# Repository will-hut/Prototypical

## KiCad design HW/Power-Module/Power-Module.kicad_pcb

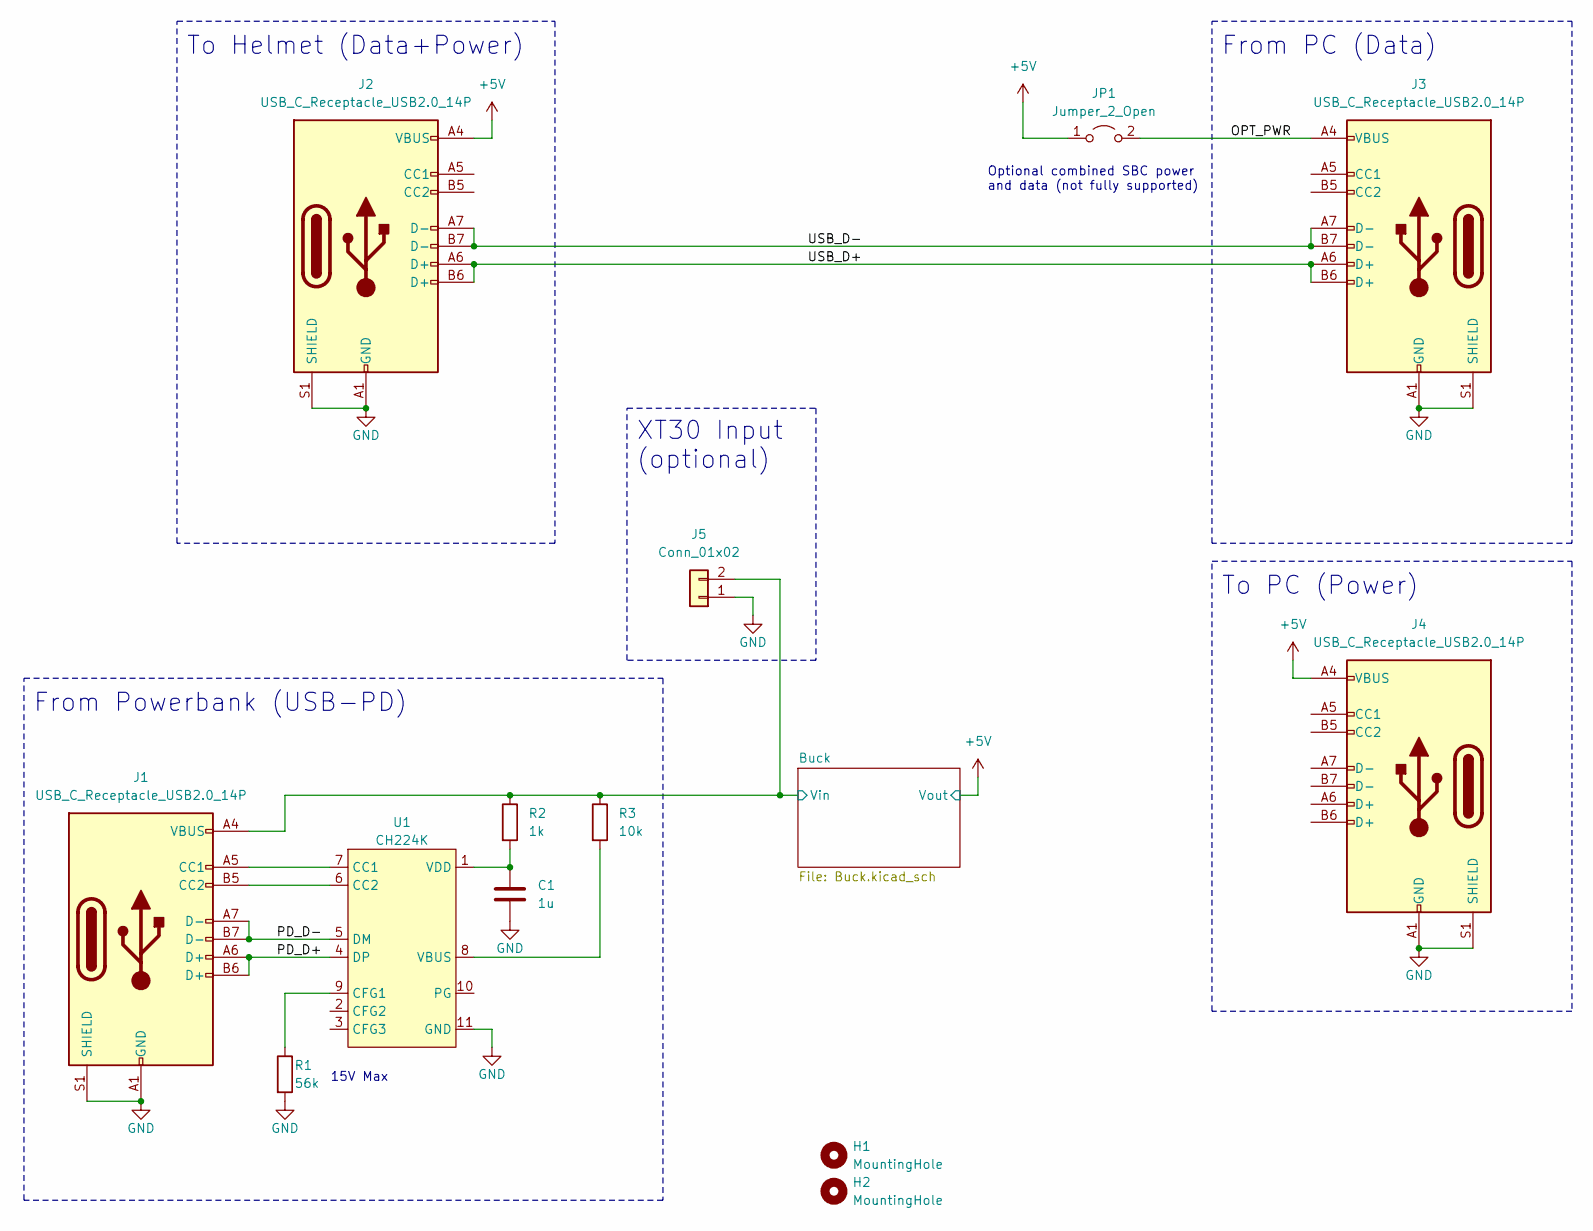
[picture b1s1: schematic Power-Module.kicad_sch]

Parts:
C1: 1u; C_0603_1608Metric; LCSC C15849
H1, H2: MountingHole; MountingHole_3.2mm_M3
J1, J2, J3, J4: USB_C_Receptacle_USB2.0_14P; USB_C_Receptacle_GCT_USB4105-xx-A_16P_TopMnt_Horizontal
J5: Conn_01x02; AMASS_XT30U-F_1x02_P5.0mm_Vertical
JP1: Jumper_2_Open; SolderJumper-2_P1.3mm_Open_Pad1.0x1.5mm
R1: 56k; R_0603_1608Metric; LCSC C23206
R2: 1k; R_0603_1608Metric; LCSC C21190
R3: 10k; R_0603_1608Metric; LCSC C25804
U1: CH224K; ESSOP-10_L4.9-W3.9-P1.0-LS6.0-TL-EP; LCSC Part C970725

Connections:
+5V: J2.A4 (VBUS), J2.A9 (VBUS), J2.B4 (VBUS), J2.B9 (VBUS), J4.A4 (VBUS), J4.A9 (VBUS), J4.B4 (VBUS), J4.B9 (VBUS), JP1.1 (A); also elsewhere on the board
/Buck/Vin: J1.A4 (VBUS), J1.A9 (VBUS), J1.B4 (VBUS), J1.B9 (VBUS), J5.2, R2.1, R3.1; also elsewhere on the board
/OPT_PWR: J3.A4 (VBUS), J3.A9 (VBUS), J3.B4 (VBUS), J3.B9 (VBUS), JP1.2 (B)
/PD_D+: J1.A6 (D+), J1.B6 (D+), U1.4 (DP)
/PD_D-: J1.A7 (D-), J1.B7 (D-), U1.5 (DM)
/USB_D+: J2.A6 (D+), J2.B6 (D+), J3.A6 (D+), J3.B6 (D+)
/USB_D-: J2.A7 (D-), J2.B7 (D-), J3.A7 (D-), J3.B7 (D-)
GND: C1.2, J1.A1 (GND), J1.A12 (GND), J1.B1 (GND), J1.B12 (GND), J1.S1 (SHIELD), J2.A1 (GND), J2.A12 (GND), J2.B1 (GND), J2.B12 (GND), J2.S1 (SHIELD), J3.A1 (GND), J3.A12 (GND), J3.B1 (GND), J3.B12 (GND), J3.S1 (SHIELD), J4.A1 (GND), J4.A12 (GND), J4.B1 (GND), J4.B12 (GND), J4.S1 (SHIELD), J5.1, R1.2, U1.11 (GND); also elsewhere on the board
unnamed: J1.A5 (CC1), U1.7 (CC1)
unnamed: J1.B5 (CC2), U1.6 (CC2)
unnamed: R1.1, U1.9 (CFG1)
unnamed: R3.2, U1.8 (VBUS)
unnamed: C1.1, R2.2, U1.1 (VDD)

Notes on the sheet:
To Helmet (Data+Power)
From PC (Data)
Optional combined SBC power and data (not fully supported)
15V Max
From Powerbank (USB-PD)
To PC (Power)
XT30 Input (optional)

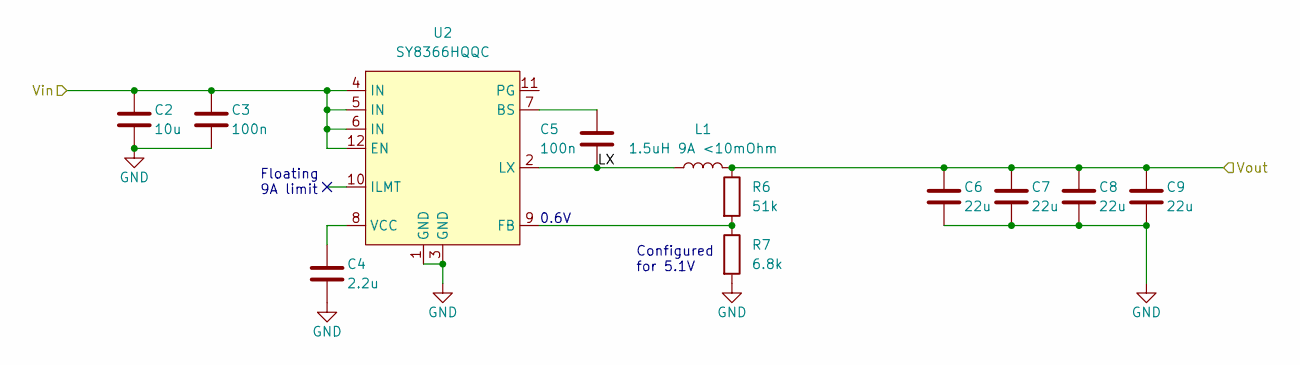
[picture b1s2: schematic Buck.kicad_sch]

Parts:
C2: 10u; C_0603_1608Metric
C3, C5: 100n; C_0603_1608Metric
C4: 2.2u; C_0603_1608Metric
C6, C7, C8, C9: 22u; C_0805_2012Metric
L1: 1.5uH 9A <10mOhm; IND-SMD_L7.0-W6.6
R6: 51k; R_0603_1608Metric
R7: 6.8k; R_0603_1608Metric
U2: SY8366HQQC; QFN-12_L3.0-W3.0-P0.45-TL-EP; LCSC Part C178253

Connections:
+5V: C6.1, C7.1, C8.1, C9.1, L1.2, R6.1; also elsewhere on the board
/Buck/LX: C5.2, L1.1, U2.2 (LX)
/Buck/Vin: C2.1, C3.1, U2.4 (IN), U2.5 (IN), U2.6 (IN), U2.12 (EN); also elsewhere on the board
GND: C2.2, C3.2, C4.2, C6.2, C7.2, C8.2, C9.2, R7.2, U2.1 (GND), U2.3 (GND); also elsewhere on the board
unnamed: C5.1, U2.7 (BS)
unnamed: R6.2, R7.1, U2.9 (FB)
unnamed: C4.1, U2.8 (VCC)

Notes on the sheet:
Floating 9A limit
0.6V
Configured for 5.1V

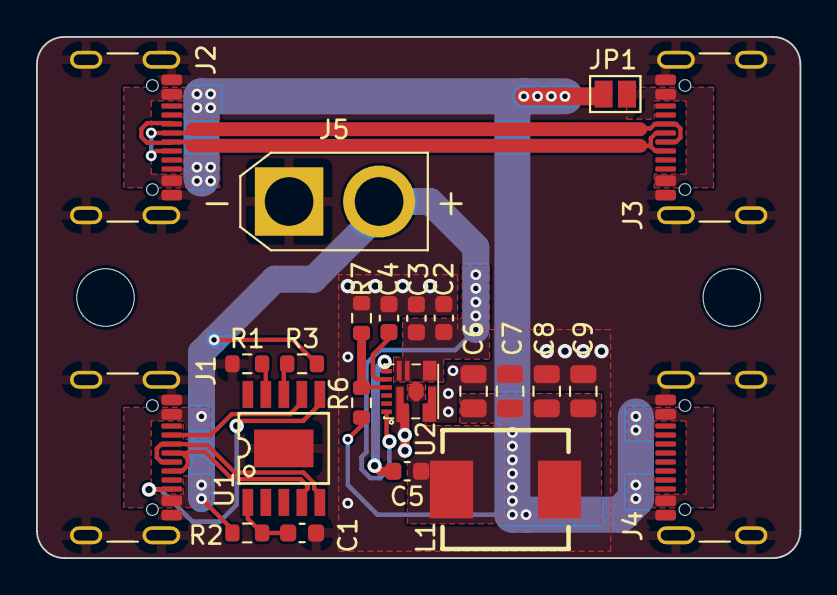
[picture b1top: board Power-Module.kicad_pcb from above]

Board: 2 copper layers, 42.4 x 29.0 mm, 25 parts (0 on the bottom side), 17 nets.

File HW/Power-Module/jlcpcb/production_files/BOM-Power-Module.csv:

Comment,Designator,Footprint,LCSC
100n,"C3,C5",C_0603_1608Metric,C14663
1u,C1,C_0603_1608Metric,C15849
1.5uH 9A <10mOhm,L1,IND-SMD_L7.0-W6.6,C167217
SY8366HQQC,U2,QFN-12_L3.0-W3.0-P0.45-TL-EP,C178253
1k,R2,R_0603_1608Metric,C21190
51k,R6,R_0603_1608Metric,C23196
56k,R1,R_0603_1608Metric,C23206
6.8k,R7,R_0603_1608Metric,C23212
2.2u,C4,C_0603_1608Metric,C23630
10k,R3,R_0603_1608Metric,C25804
22u,"C6,C7,C8,C9",C_0805_2012Metric,C45783
10u,C2,C_0603_1608Metric,C96446
CH224K,U1,ESSOP-10_L4.9-W3.9-P1.0-LS6.0-TL-EP,C970725
MountingHole,H2,MountingHole_3.2mm_M3,
MountingHole,H1,MountingHole_3.2mm_M3,
Jumper_2_Open,JP1,SolderJumper-2_P1.3mm_Open_Pad1.0x1.5mm,
USB_C_Receptacle_USB2.0_14P,J2,USB_C_Receptacle_GCT_USB4105-xx-A_16P_TopMnt_Horizontal,
USB_C_Receptacle_USB2.0_14P,J3,USB_C_Receptacle_GCT_USB4105-xx-A_16P_TopMnt_Horizontal,
USB_C_Receptacle_USB2.0_14P,J4,USB_C_Receptacle_GCT_USB4105-xx-A_16P_TopMnt_Horizontal,
USB_C_Receptacle_USB2.0_14P,J1,USB_C_Receptacle_GCT_USB4105-xx-A_16P_TopMnt_Horizontal,
Conn_01x02,J5,AMASS_XT30U-F_1x02_P5.0mm_Vertical,

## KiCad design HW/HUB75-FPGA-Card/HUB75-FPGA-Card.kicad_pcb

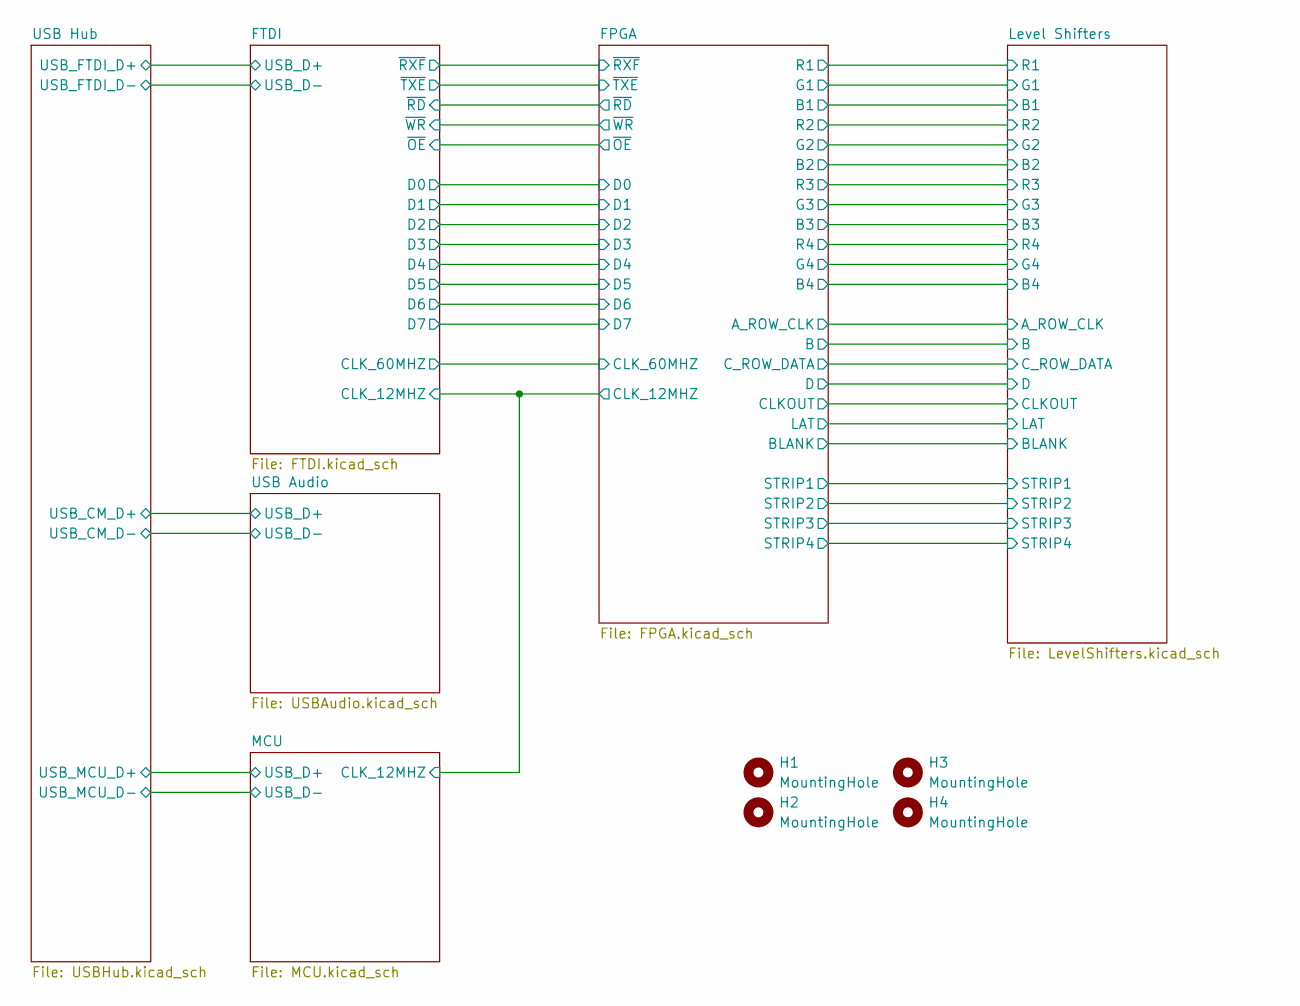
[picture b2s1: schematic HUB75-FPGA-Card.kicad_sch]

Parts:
H1, H2, H3, H4: MountingHole; MountingHole_3.2mm_M3

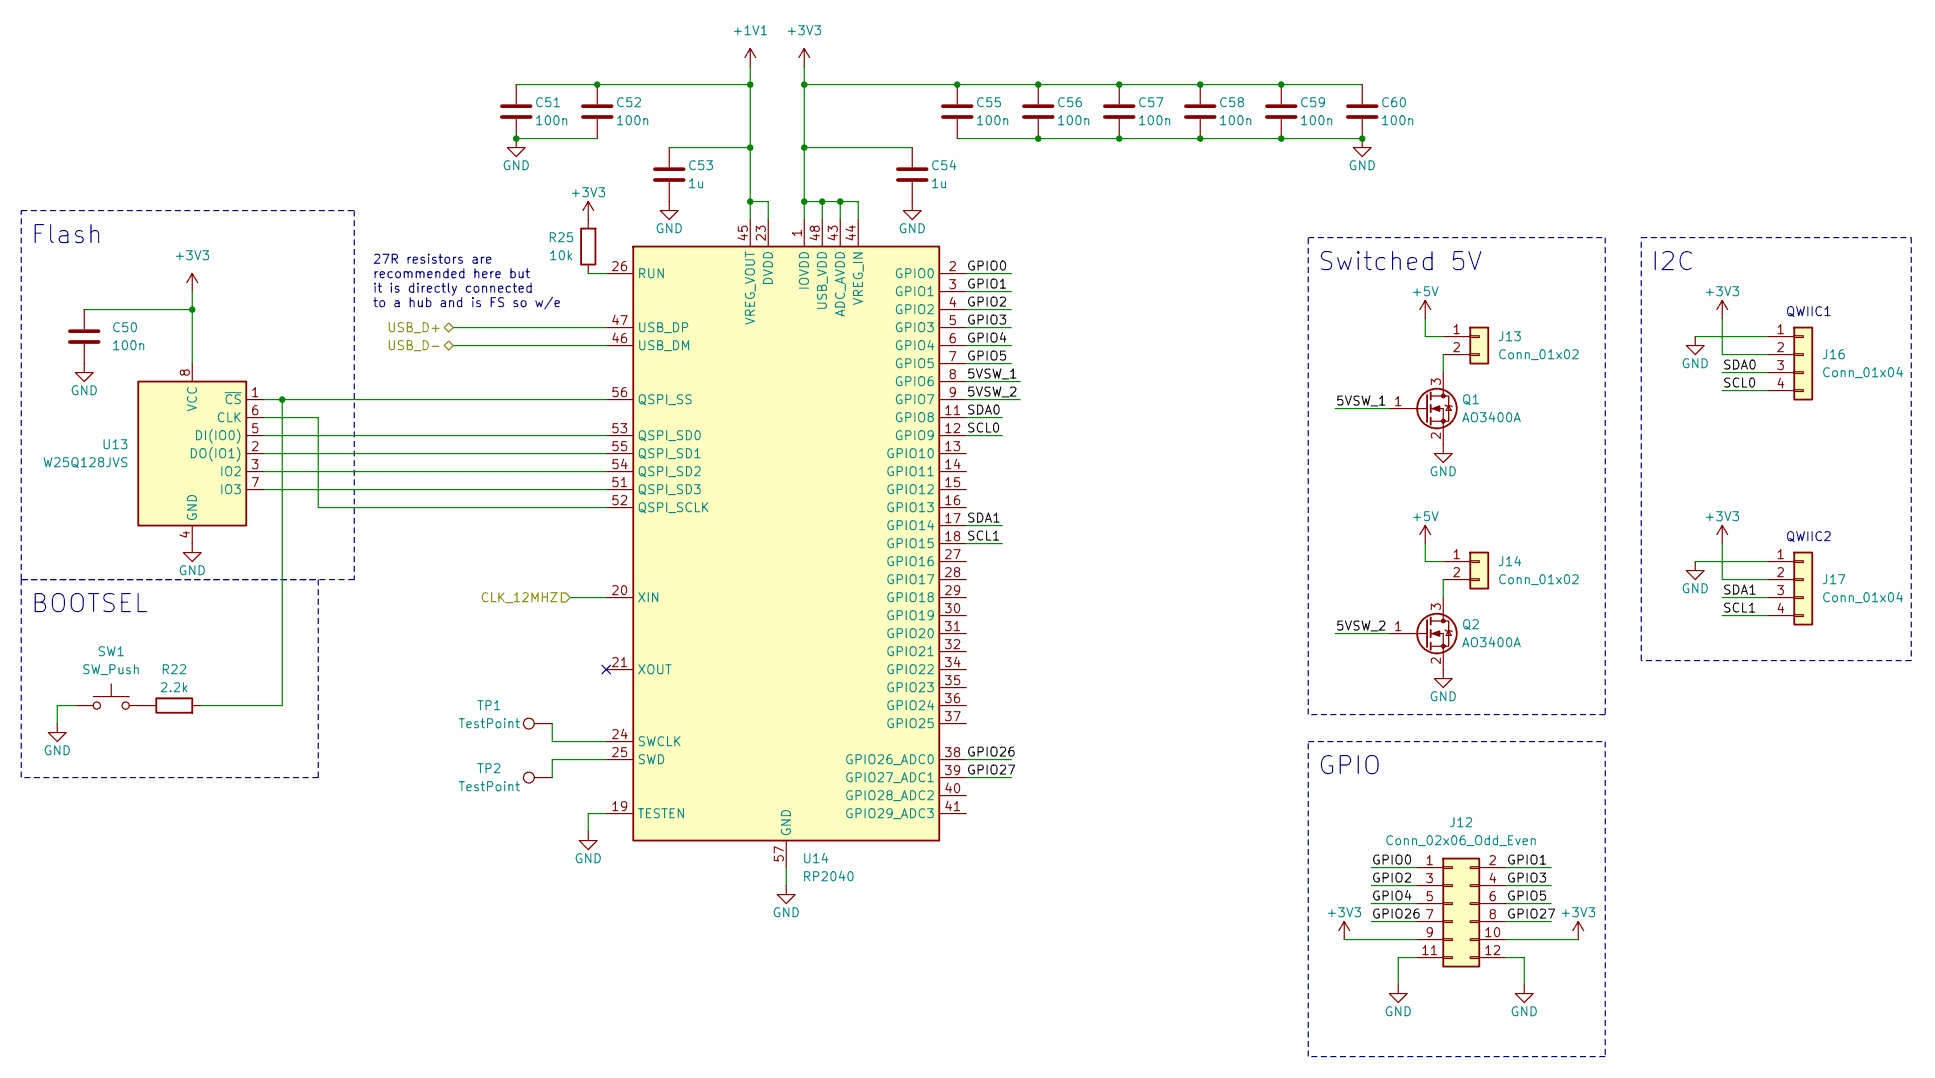
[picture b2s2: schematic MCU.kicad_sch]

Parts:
C50, C51, C52, C55, C56, C57, C58, C59, C60: 100n; C_0603_1608Metric
C53, C54: 1u; C_0603_1608Metric
J12: Conn_02x06_Odd_Even; PinHeader_2x06_P2.54mm_Vertical
J13, J14: Conn_01x02; PinHeader_1x02_P2.54mm_Vertical
J16, J17: Conn_01x04; JST_SH_BM04B-SRSS-TB_1x04-1MP_P1.00mm_Vertical
Q1, Q2: AO3400A; SOT-23
R22: 2.2k; R_0603_1608Metric
R25: 10k; R_0603_1608Metric
SW1: SW_Push; SW_TS-1187A-B-A-B
TP1, TP2: TestPoint; TestPoint_Pad_D1.0mm
U13: W25Q128JVS; SOIC-8_5.23x5.23mm_P1.27mm
U14: RP2040; QFN-56-1EP_7x7mm_P0.4mm_EP3.2x3.2mm

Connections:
+1V1: C51.1, C52.1, C53.1, U14.23 (DVDD), U14.45 (VREG_VOUT), U14.50 (DVDD)
+3V3: C50.1, C54.1, C55.1, C56.1, C57.1, C58.1, C59.1, C60.1, J12.9, J12.10, J16.2, J17.2, R25.2, U13.8 (VCC), U14.1 (IOVDD), U14.10 (IOVDD), U14.22 (IOVDD), U14.33 (IOVDD), U14.42 (IOVDD), U14.43 (ADC_AVDD), U14.44 (VREG_IN), U14.48 (USB_VDD), U14.49 (IOVDD); also elsewhere on the board
+5V: J13.1, J14.1; also elsewhere on the board
/FPGA/CLK_12MHZ: U14.20 (XIN); also elsewhere on the board
/MCU/5VSW_1: Q1.1 (G), U14.8 (GPIO6)
/MCU/5VSW_2: Q2.1 (G), U14.9 (GPIO7)
/MCU/GPIO0: J12.1, U14.2 (GPIO0)
/MCU/GPIO1: J12.2, U14.3 (GPIO1)
/MCU/GPIO2: J12.3, U14.4 (GPIO2)
/MCU/GPIO3: J12.4, U14.5 (GPIO3)
/MCU/GPIO4: J12.5, U14.6 (GPIO4)
/MCU/GPIO5: J12.6, U14.7 (GPIO5)
/MCU/GPIO26: J12.7, U14.38 (GPIO26_ADC0)
/MCU/GPIO27: J12.8, U14.39 (GPIO27_ADC1)
/MCU/SCL0: J16.4, U14.12 (GPIO9)
/MCU/SCL1: J17.4, U14.18 (GPIO15)
/MCU/SDA0: J16.3, U14.11 (GPIO8)
/MCU/SDA1: J17.3, U14.17 (GPIO14)
/MCU/USB_D+: U14.47 (USB_DP); also elsewhere on the board
/MCU/USB_D-: U14.46 (USB_DM); also elsewhere on the board
GND: C50.2, C51.2, C52.2, C53.2, C54.2, C55.2, C56.2, C57.2, C58.2, C59.2, C60.2, J12.11, J12.12, J16.1, J17.1, Q1.2 (S), Q2.2 (S), SW1.1, U13.4 (GND), U14.19 (TESTEN), U14.57 (GND); also elsewhere on the board
unnamed: J13.2, Q1.3 (D)
unnamed: J14.2, Q2.3 (D)
unnamed: R22.1, SW1.2
unnamed: U13.6 (CLK), U14.52 (QSPI_SCLK)
unnamed: U13.5 (DI(IO0)), U14.53 (QSPI_SD0)
unnamed: U13.2 (DO(IO1)), U14.55 (QSPI_SD1)
unnamed: U13.3 (IO2), U14.54 (QSPI_SD2)
unnamed: U13.7 (IO3), U14.51 (QSPI_SD3)
unnamed: R22.2, U13.1 (~CS), U14.56 (QSPI_SS)
unnamed: R25.1, U14.26 (RUN)
unnamed: TP1.1, U14.24 (SWCLK)
unnamed: TP2.1, U14.25 (SWD)

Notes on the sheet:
Flash
QWIIC2
27R resistors are recommended here but it is directly connected to a hub and is FS so w/e
I2C
GPIO
Switched 5V
QWIIC1
BOOTSEL

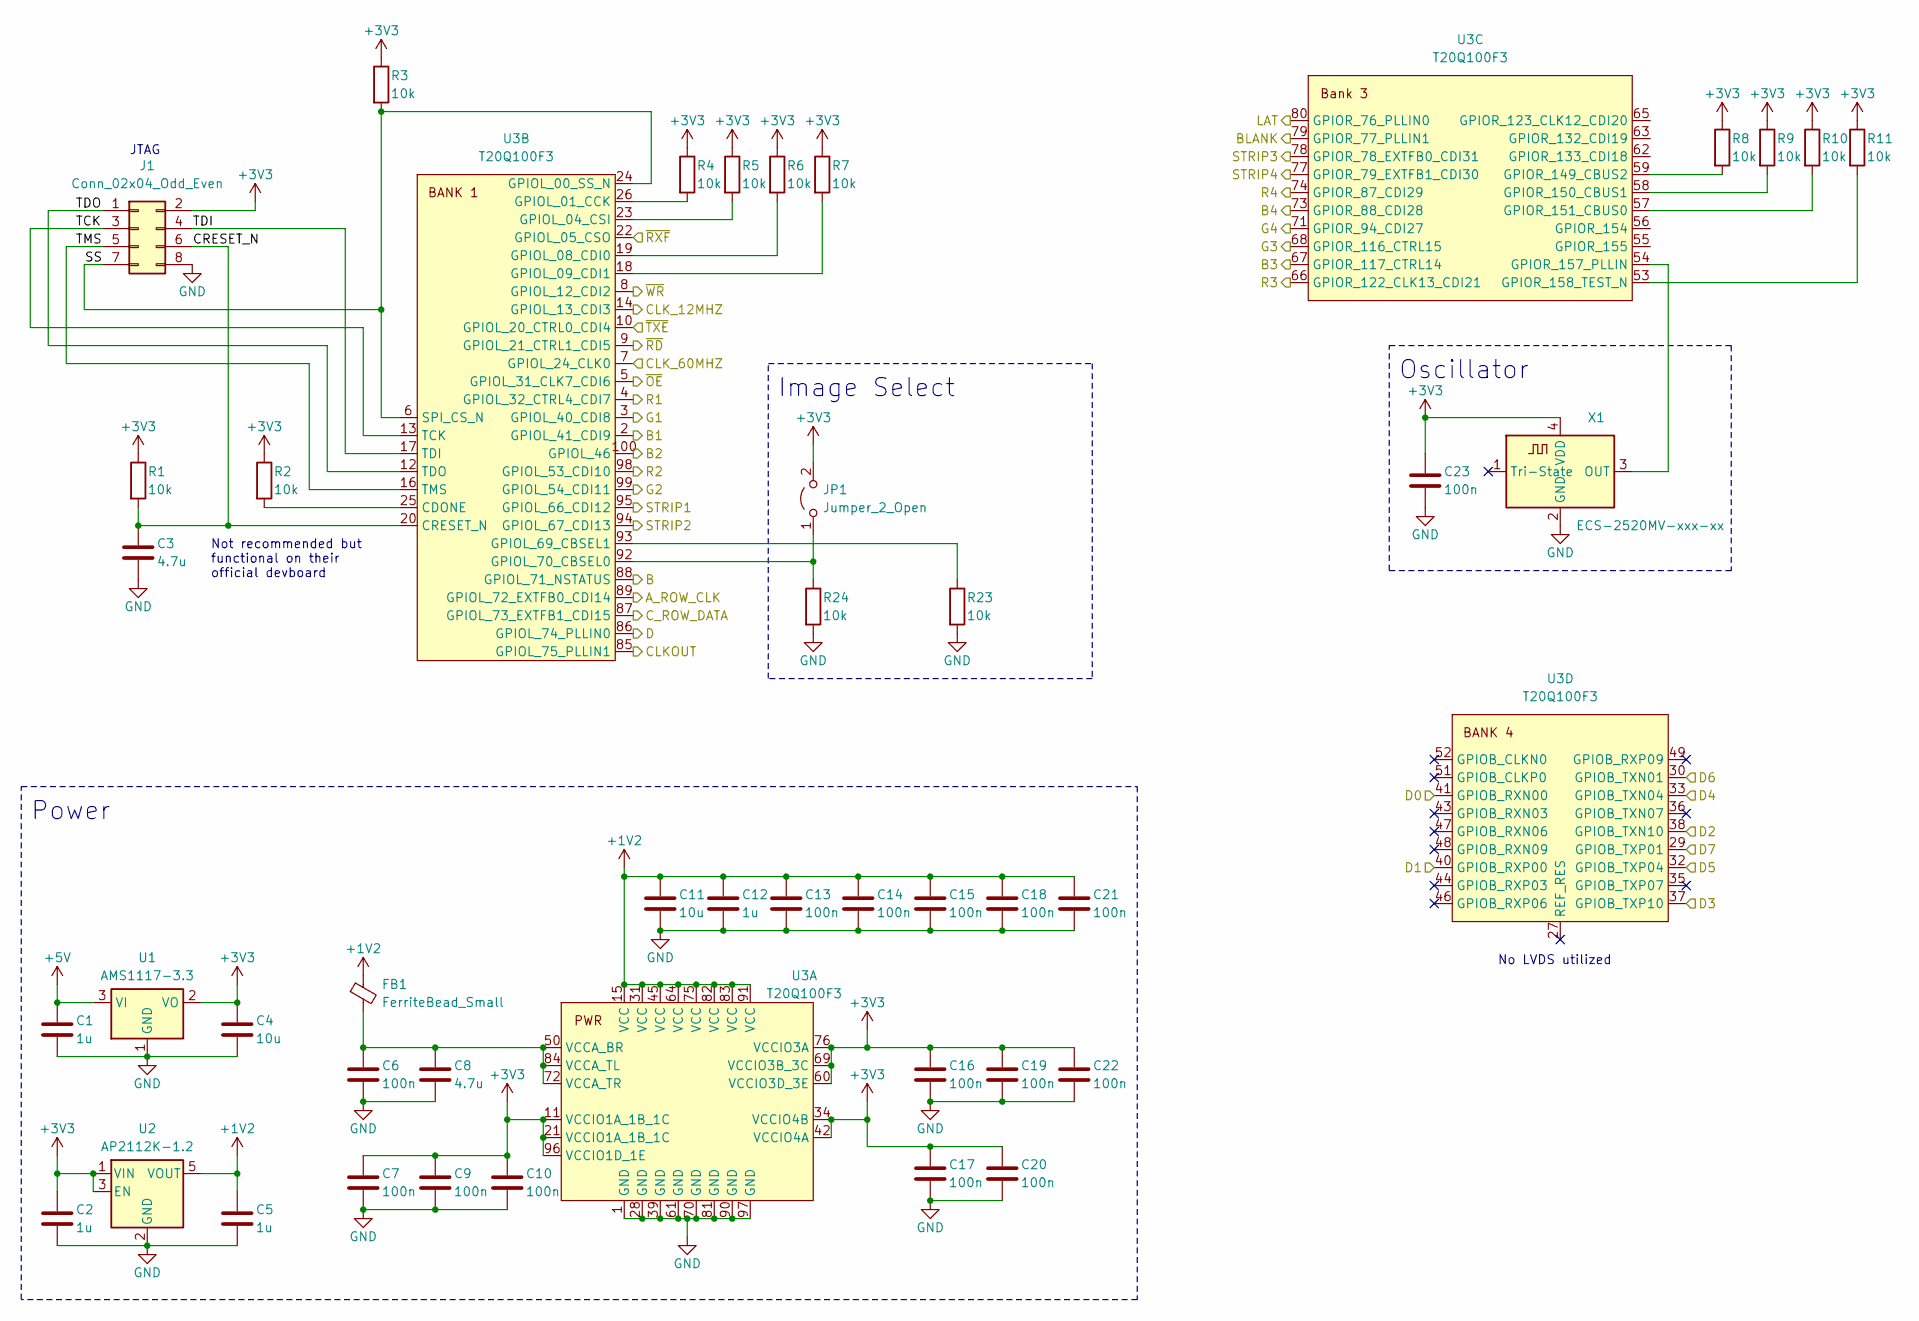
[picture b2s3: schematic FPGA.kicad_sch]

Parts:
C1, C2, C5, C12: 1u; C_0603_1608Metric
C3, C8: 4.7u; C_0603_1608Metric
C4, C11: 10u; C_0603_1608Metric
C6, C7, C9, C10, C13, C14, C15, C16, C17, C18, C19, C20, C21, C22, C23: 100n; C_0603_1608Metric
FB1: FerriteBead_Small; R_0603_1608Metric
J1: Conn_02x04_Odd_Even; PinHeader_2x04_P2.54mm_Vertical
JP1: Jumper_2_Open; PinHeader_1x02_P2.54mm_Vertical
R1, R2, R3, R4, R5, R6, R7, R8, R9, R10, R11, R23, R24: 10k; R_0603_1608Metric
U1: AMS1117-3.3; SOT-223-3_TabPin2
U2: AP2112K-1.2; SOT-23-5
U3: T20Q100F3; TQFP-100_14x14mm_P0.5mm
X1: ECS-2520MV-xxx-xx; Oscillator_SMD_ECS_2520MV-xxx-xx-4Pin_2.5x2.0mm

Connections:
+1V2: C5.1, C11.1, C12.1, C13.1, C14.1, C15.1, C18.1, C21.1, FB1.1, U2.5 (VOUT), U3.15 (VCC), U3.31 (VCC), U3.45 (VCC), U3.64 (VCC), U3.75 (VCC), U3.82 (VCC), U3.83 (VCC), U3.91 (VCC)
+3V3: C2.1, C4.1, C7.1, C9.1, C10.1, C16.1, C17.1, C19.1, C20.1, C22.1, C23.1, J1.2, JP1.2 (B), R1.1, R2.1, R3.1, R4.1, R5.1, R6.1, R7.1, R8.1, R9.1, R10.1, R11.1, U1.2 (VO), U2.1 (VIN), U2.3 (EN), U3.11 (VCCIO1A_1B_1C), U3.21 (VCCIO1A_1B_1C), U3.34 (VCCIO4B), U3.42 (VCCIO4A), U3.60 (VCCIO3D_3E), U3.69 (VCCIO3B_3C), U3.76 (VCCIO3A), U3.96 (VCCIO1D_1E), X1.4 (VDD); also elsewhere on the board
+5V: C1.1, U1.3 (VI); also elsewhere on the board
/FPGA/A_ROW_CLK: U3.89 (GPIOL_72_EXTFB0_CDI14); also elsewhere on the board
/FPGA/B: U3.88 (GPIOL_71_NSTATUS); also elsewhere on the board
/FPGA/B1: U3.2 (GPIOL_41_CDI9); also elsewhere on the board
/FPGA/B2: U3.100 (GPIOL_46); also elsewhere on the board
/FPGA/B3: U3.67 (GPIOR_117_CTRL14); also elsewhere on the board
/FPGA/B4: U3.73 (GPIOR_88_CDI28); also elsewhere on the board
/FPGA/BLANK: U3.79 (GPIOR_77_PLLIN1); also elsewhere on the board
/FPGA/CLKOUT: U3.85 (GPIOL_75_PLLIN1); also elsewhere on the board
/FPGA/CLK_12MHZ: U3.14 (GPIOL_13_CDI3); also elsewhere on the board
/FPGA/CLK_60MHZ: U3.7 (GPIOL_24_CLK0); also elsewhere on the board
/FPGA/CRESET_N: C3.1, J1.6, R1.2, U3.20 (CRESET_N)
/FPGA/C_ROW_DATA: U3.87 (GPIOL_73_EXTFB1_CDI15); also elsewhere on the board
/FPGA/D: U3.86 (GPIOL_74_PLLIN0); also elsewhere on the board
/FPGA/D0: U3.41 (GPIOB_RXN00); also elsewhere on the board
/FPGA/D1: U3.40 (GPIOB_RXP00); also elsewhere on the board
/FPGA/D2: U3.38 (GPIOB_TXN10); also elsewhere on the board
/FPGA/D3: U3.37 (GPIOB_TXP10); also elsewhere on the board
/FPGA/D4: U3.33 (GPIOB_TXN04); also elsewhere on the board
/FPGA/D5: U3.32 (GPIOB_TXP04); also elsewhere on the board
/FPGA/D6: U3.30 (GPIOB_TXN01); also elsewhere on the board
/FPGA/D7: U3.29 (GPIOB_TXP01); also elsewhere on the board
/FPGA/G1: U3.3 (GPIOL_40_CDI8); also elsewhere on the board
/FPGA/G2: U3.99 (GPIOL_54_CDI11); also elsewhere on the board
/FPGA/G3: U3.68 (GPIOR_116_CTRL15); also elsewhere on the board
/FPGA/G4: U3.71 (GPIOR_94_CDI27); also elsewhere on the board
/FPGA/LAT: U3.80 (GPIOR_76_PLLIN0); also elsewhere on the board
/FPGA/R1: U3.4 (GPIOL_32_CTRL4_CDI7); also elsewhere on the board
/FPGA/R2: U3.98 (GPIOL_53_CDI10); also elsewhere on the board
/FPGA/R3: U3.66 (GPIOR_122_CLK13_CDI21); also elsewhere on the board
/FPGA/R4: U3.74 (GPIOR_87_CDI29); also elsewhere on the board
/FPGA/SS: J1.7, R3.2, U3.6 (SPI_CS_N), U3.24 (GPIOL_00_SS_N)
/FPGA/STRIP1: U3.95 (GPIOL_66_CDI12); also elsewhere on the board
/FPGA/STRIP2: U3.94 (GPIOL_67_CDI13); also elsewhere on the board
/FPGA/STRIP3: U3.78 (GPIOR_78_EXTFB0_CDI31); also elsewhere on the board
/FPGA/STRIP4: U3.77 (GPIOR_79_EXTFB1_CDI30); also elsewhere on the board
/FPGA/TCK: J1.3, U3.13 (TCK)
/FPGA/TDI: J1.4, U3.17 (TDI)
/FPGA/TDO: J1.1, U3.12 (TDO)
/FPGA/TMS: J1.5, U3.16 (TMS)
/FPGA/~OE: U3.5 (GPIOL_31_CLK7_CDI6); also elsewhere on the board
/FPGA/~RD: U3.9 (GPIOL_21_CTRL1_CDI5); also elsewhere on the board
/FPGA/~RXF: U3.22 (GPIOL_05_CSO); also elsewhere on the board
/FPGA/~TXE: U3.10 (GPIOL_20_CTRL0_CDI4); also elsewhere on the board
/FPGA/~WR: U3.8 (GPIOL_12_CDI2); also elsewhere on the board
GND: C1.2, C2.2, C3.2, C4.2, C5.2, C6.2, C7.2, C8.2, C9.2, C10.2, C11.2, C12.2, C13.2, C14.2, C15.2, C16.2, C17.2, C18.2, C19.2, C20.2, C21.2, C22.2, C23.2, J1.8, R23.2, R24.2, U1.1 (GND), U2.2 (GND), U3.1 (GND), U3.28 (GND), U3.39 (GND), U3.61 (GND), U3.70 (GND), U3.81 (GND), U3.90 (GND), U3.97 (GND), X1.2 (GND); also elsewhere on the board
unnamed: JP1.1 (A), R24.1, U3.92 (GPIOL_70_CBSEL0)
unnamed: C6.1, C8.1, FB1.2, U3.50 (VCCA_BR), U3.72 (VCCA_TR), U3.84 (VCCA_TL)
unnamed: R2.2, U3.25 (CDONE)
unnamed: R4.2, U3.26 (GPIOL_01_CCK)
unnamed: R5.2, U3.23 (GPIOL_04_CSI)
unnamed: R6.2, U3.19 (GPIOL_08_CDI0)
unnamed: R7.2, U3.18 (GPIOL_09_CDI1)
unnamed: R23.1, U3.93 (GPIOL_69_CBSEL1)
unnamed: R8.2, U3.59 (GPIOR_149_CBUS2)
unnamed: R9.2, U3.58 (GPIOR_150_CBUS1)
unnamed: R10.2, U3.57 (GPIOR_151_CBUS0)
unnamed: U3.54 (GPIOR_157_PLLIN), X1.3 (OUT)
unnamed: R11.2, U3.53 (GPIOR_158_TEST_N)

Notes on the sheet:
Image Select
JTAG
Power
No LVDS utilized
Not recommended but functional on their official devboard
Oscillator

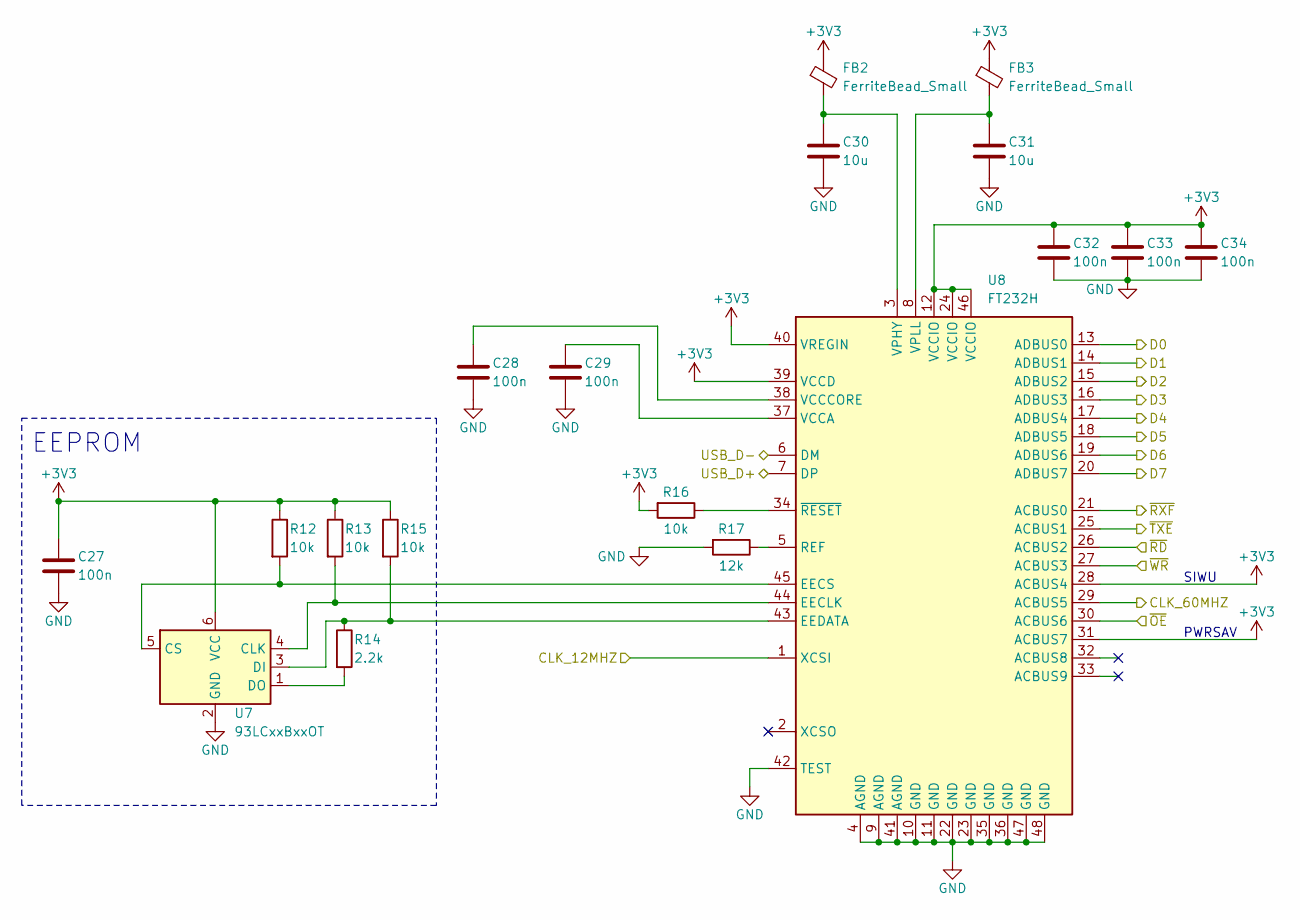
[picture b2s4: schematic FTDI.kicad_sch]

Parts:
C27, C28, C29, C32, C33, C34: 100n; C_0603_1608Metric
C30, C31: 10u; C_0603_1608Metric
FB2, FB3: FerriteBead_Small; R_0603_1608Metric
R12, R13, R15, R16: 10k; R_0603_1608Metric
R14: 2.2k; R_0603_1608Metric
R17: 12k; R_0603_1608Metric
U7: 93LCxxBxxOT; SOT-23-6
U8: FT232H; LQFP-48_7x7mm_P0.5mm

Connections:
+3V3: C27.1, C32.1, C33.1, C34.1, FB2.1, FB3.1, R12.1, R13.1, R15.1, R16.2, U7.6 (VCC), U8.12 (VCCIO), U8.24 (VCCIO), U8.28 (ACBUS4), U8.31 (ACBUS7), U8.39 (VCCD), U8.40 (VREGIN), U8.46 (VCCIO); also elsewhere on the board
/FPGA/CLK_12MHZ: U8.1 (XCSI); also elsewhere on the board
/FPGA/CLK_60MHZ: U8.29 (ACBUS5); also elsewhere on the board
/FPGA/D0: U8.13 (ADBUS0); also elsewhere on the board
/FPGA/D1: U8.14 (ADBUS1); also elsewhere on the board
/FPGA/D2: U8.15 (ADBUS2); also elsewhere on the board
/FPGA/D3: U8.16 (ADBUS3); also elsewhere on the board
/FPGA/D4: U8.17 (ADBUS4); also elsewhere on the board
/FPGA/D5: U8.18 (ADBUS5); also elsewhere on the board
/FPGA/D6: U8.19 (ADBUS6); also elsewhere on the board
/FPGA/D7: U8.20 (ADBUS7); also elsewhere on the board
/FPGA/~OE: U8.30 (ACBUS6); also elsewhere on the board
/FPGA/~RD: U8.26 (ACBUS2); also elsewhere on the board
/FPGA/~RXF: U8.21 (ACBUS0); also elsewhere on the board
/FPGA/~TXE: U8.25 (ACBUS1); also elsewhere on the board
/FPGA/~WR: U8.27 (ACBUS3); also elsewhere on the board
/FTDI/USB_D+: U8.7 (DP); also elsewhere on the board
/FTDI/USB_D-: U8.6 (DM); also elsewhere on the board
GND: C27.2, C28.2, C29.2, C30.2, C31.2, C32.2, C33.2, C34.2, R17.2, U7.2 (GND), U8.4 (AGND), U8.9 (AGND), U8.10 (GND), U8.11 (GND), U8.22 (GND), U8.23 (GND), U8.35 (GND), U8.36 (GND), U8.41 (AGND), U8.42 (TEST), U8.47 (GND), U8.48 (GND); also elsewhere on the board
unnamed: R13.2, U7.4 (CLK), U8.44 (EECLK)
unnamed: R12.2, U7.5 (CS), U8.45 (EECS)
unnamed: R14.1, R15.2, U7.3 (DI), U8.43 (EEDATA)
unnamed: R14.2, U7.1 (DO)
unnamed: R17.1, U8.5 (REF)
unnamed: C29.1, U8.37 (VCCA)
unnamed: C28.1, U8.38 (VCCCORE)
unnamed: C30.1, FB2.2, U8.3 (VPHY)
unnamed: C31.1, FB3.2, U8.8 (VPLL)
unnamed: R16.1, U8.34 (~RESET)

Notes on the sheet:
SIWU
EEPROM
PWRSAV

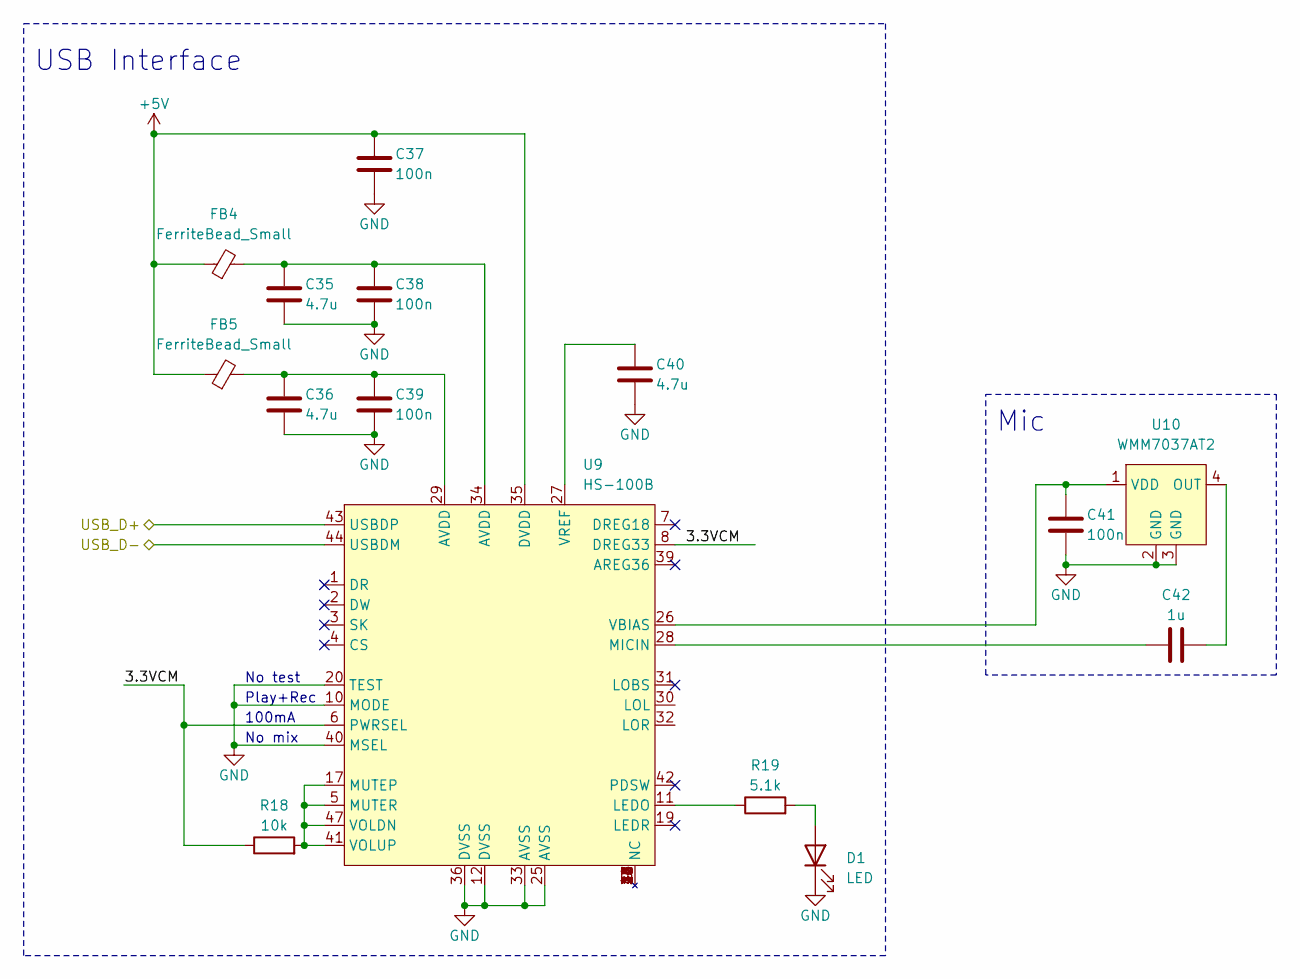
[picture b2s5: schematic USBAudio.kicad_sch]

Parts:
C35, C36, C40: 4.7u; C_0603_1608Metric
C37, C38, C39, C41: 100n; C_0603_1608Metric
C42: 1u; C_0603_1608Metric
D1: LED; D_0603_1608Metric
FB4, FB5: FerriteBead_Small; R_0603_1608Metric
R18: 10k; R_0603_1608Metric
R19: 5.1k; R_0603_1608Metric
U9: HS-100B; LQFP-48_7x7mm_P0.5mm
U10: WMM7037AT2

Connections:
+5V: C37.1, FB4.1, FB5.1, U9.35 (DVDD); also elsewhere on the board
/USB Audio/3.3VCM: R18.1, U9.6 (PWRSEL), U9.8 (DREG33)
/USB Audio/USB_D+: U9.43 (USBDP); also elsewhere on the board
/USB Audio/USB_D-: U9.44 (USBDM); also elsewhere on the board
GND: C35.2, C36.2, C37.2, C38.2, C39.2, C40.2, C41.2, D1.1 (K), U9.10 (MODE), U9.12 (DVSS), U9.20 (TEST), U9.25 (AVSS), U9.33 (AVSS), U9.36 (DVSS), U9.40 (MSEL), U10.2 (GND), U10.3 (GND); also elsewhere on the board
unnamed: C35.1, C38.1, FB4.2, U9.34 (AVDD)
unnamed: C36.1, C39.1, FB5.2, U9.29 (AVDD)
unnamed: D1.2 (A), R19.2
unnamed: R19.1, U9.11 (LEDO)
unnamed: C42.1, U9.28 (MICIN)
unnamed: R18.2, U9.5 (MUTER), U9.17 (MUTEP), U9.41 (VOLUP), U9.47 (VOLDN)
unnamed: C40.1, U9.27 (VREF)
unnamed: C42.2, U10.4 (OUT)
unnamed: C41.1, U9.26 (VBIAS), U10.1 (VDD)

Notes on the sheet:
No test
100mA
USB Interface
Mic
No mix
Play+Rec
